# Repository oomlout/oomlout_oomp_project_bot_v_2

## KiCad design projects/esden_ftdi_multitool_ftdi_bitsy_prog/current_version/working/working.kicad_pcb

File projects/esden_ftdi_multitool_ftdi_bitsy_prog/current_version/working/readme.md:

# ftdi_multitool
 
## summary 
* id: esden_ftdi_multitool_ftdi_bitsy_prog
* user: esden
* name: ftdi_multitool
* board: ftdi_bitsy_prog
* repo: https://github.com/esden/ftdi-multitool
* src_file_repo_kicad_pcb: adapters/bitsy-prog/v1.0a/ftdi-bitsy-prog.kicad_pcb
* src_file_repo_kicad_pcb_link: https://github.com/esden/ftdi-multitool/tree/master/adapters/bitsy-prog/v1.0a/ftdi-bitsy-prog.kicad_pcb

* src_file_repo_sch: adapters/bitsy-prog/v1.0a/ftdi-bitsy-prog.sch
* src_file_repo_sch_link: https://github.com/esden/ftdi-multitool/tree/master/adapters/bitsy-prog/v1.0a/ftdi-bitsy-prog.sch
* full details link: https://github.com/oomlout/oomlout_oomp_project_bot_v_2/tree/main/projects/esden_ftdi_multitool_ftdi_bitsy_prog/current_version/working

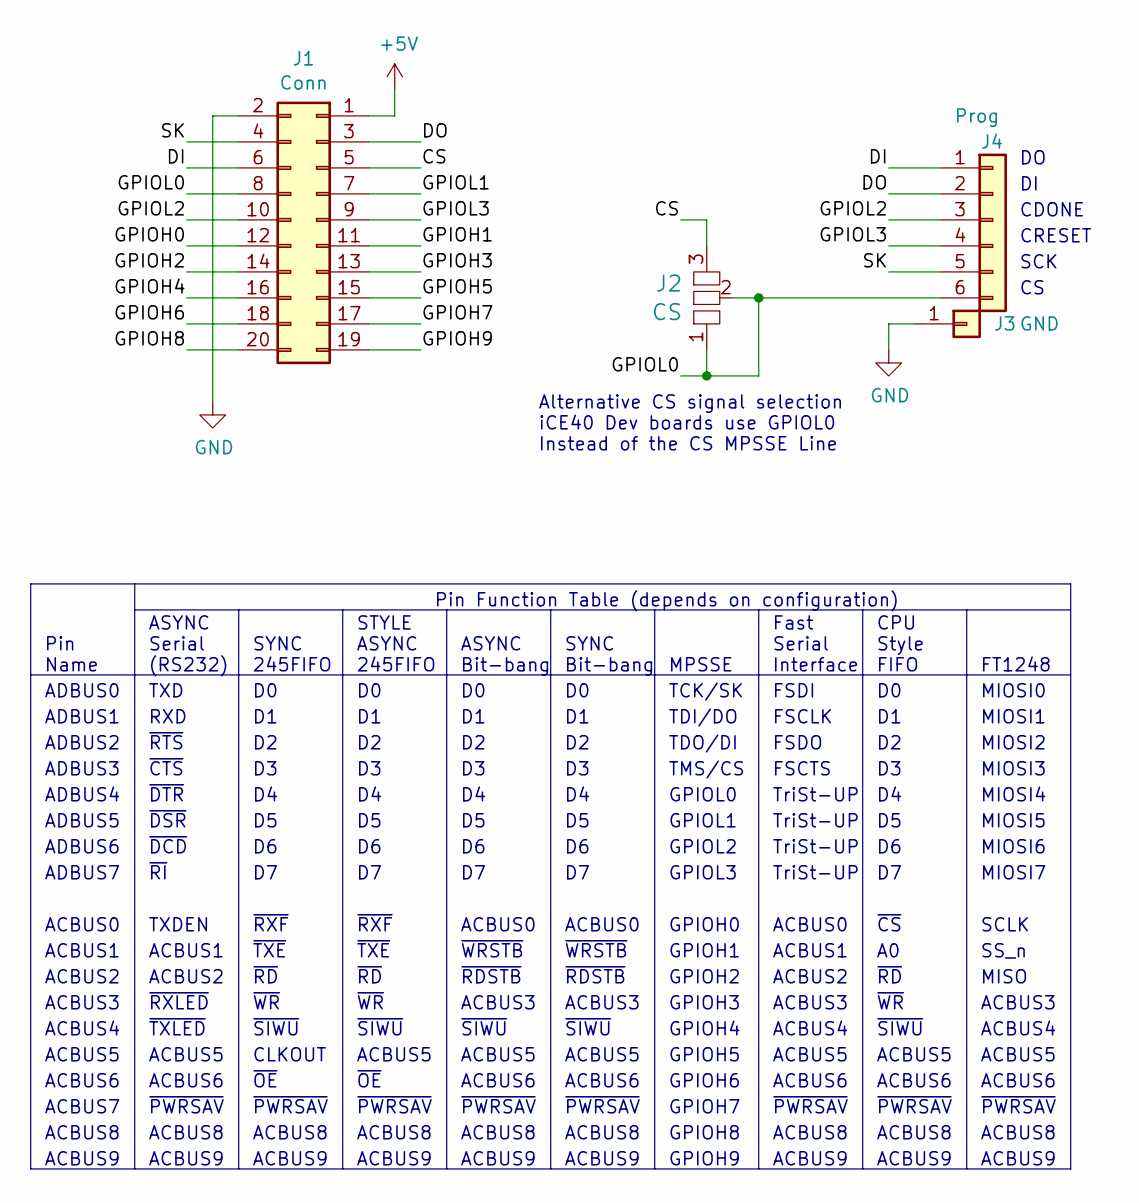
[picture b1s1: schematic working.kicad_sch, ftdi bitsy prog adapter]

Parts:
J1: Conn; FTSH-EDGE-20pin
J2: CS; J_0602
J3: GND; PinSocket_1x01_P2.54mm_Vertical
J4: Prog; PinSocket_1x06_P2.54mm_Vertical

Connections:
+5V: J1.1
/CS: J1.5, J2.3
/DI: J1.6, J4.1
/DO: J1.3, J4.2
/GPIOH0: J1.12
/GPIOH1: J1.11
/GPIOH2: J1.14
/GPIOH3: J1.13
/GPIOH4: J1.16
/GPIOH5: J1.15
/GPIOH6: J1.18
/GPIOH7: J1.17
/GPIOH8: J1.20
/GPIOH9: J1.19
/GPIOL0: J1.8, J2.1, J2.2, J4.6
/GPIOL1: J1.7
/GPIOL2: J1.10, J4.3
/GPIOL3: J1.9, J4.4
/SK: J1.4, J4.5
GND: J1.2, J3.1

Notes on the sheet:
ADBUS7
ACBUS6
~{RDSTB}
~{RTS}
ACBUS1
GPIOH8
GPIOH1
ACBUS9
~{RD}
SS_n
CPU Style FIFO
~{SIWU}
~{WRSTB}
ADBUS3
SCK
ACBUS5
~{OE}
~{CS}
GPIOL1
~{PWRSAV}
ACBUS8
MPSSE
TriSt-UP
GPIOH6
FSCLK
SYNC 245FIFO
RXD
ADBUS1
SYNC Bit-bang
~{WR}
Pin Name
~{CTS}
MIOSI6
GPIOL2
ACBUS3
~{TXE}
GPIOH5
TXDEN
TMS/CS
FSDO

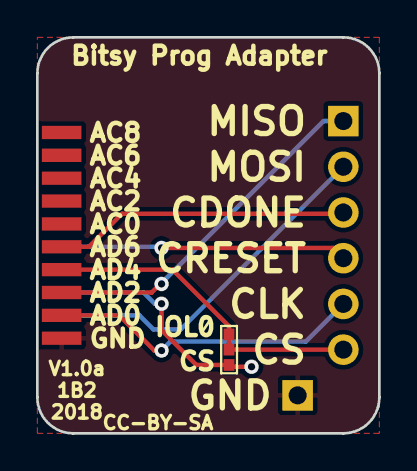
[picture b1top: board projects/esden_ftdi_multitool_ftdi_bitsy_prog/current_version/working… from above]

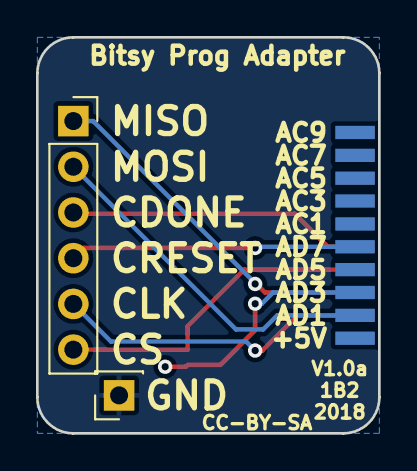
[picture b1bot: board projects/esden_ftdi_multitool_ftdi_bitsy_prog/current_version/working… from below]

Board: 2 copper layers, 19.0 x 22.0 mm, 4 parts (3 on the bottom side), 8 nets.

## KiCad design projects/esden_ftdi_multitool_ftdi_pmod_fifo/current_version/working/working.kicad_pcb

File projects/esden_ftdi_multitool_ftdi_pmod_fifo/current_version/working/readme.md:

# ftdi_multitool
 
## summary 
* id: esden_ftdi_multitool_ftdi_pmod_fifo
* user: esden
* name: ftdi_multitool
* board: ftdi_pmod_fifo
* repo: https://github.com/esden/ftdi-multitool
* src_file_repo_kicad_pcb: adapters/pmod-fifo/v1.0a/ftdi-pmod-fifo.kicad_pcb
* src_file_repo_kicad_pcb_link: https://github.com/esden/ftdi-multitool/tree/master/adapters/pmod-fifo/v1.0a/ftdi-pmod-fifo.kicad_pcb

* src_file_repo_sch: adapters/pmod-fifo/v1.0a/ftdi-pmod-fifo.sch
* src_file_repo_sch_link: https://github.com/esden/ftdi-multitool/tree/master/adapters/pmod-fifo/v1.0a/ftdi-pmod-fifo.sch
* full details link: https://github.com/oomlout/oomlout_oomp_project_bot_v_2/tree/main/projects/esden_ftdi_multitool_ftdi_pmod_fifo/current_version/working

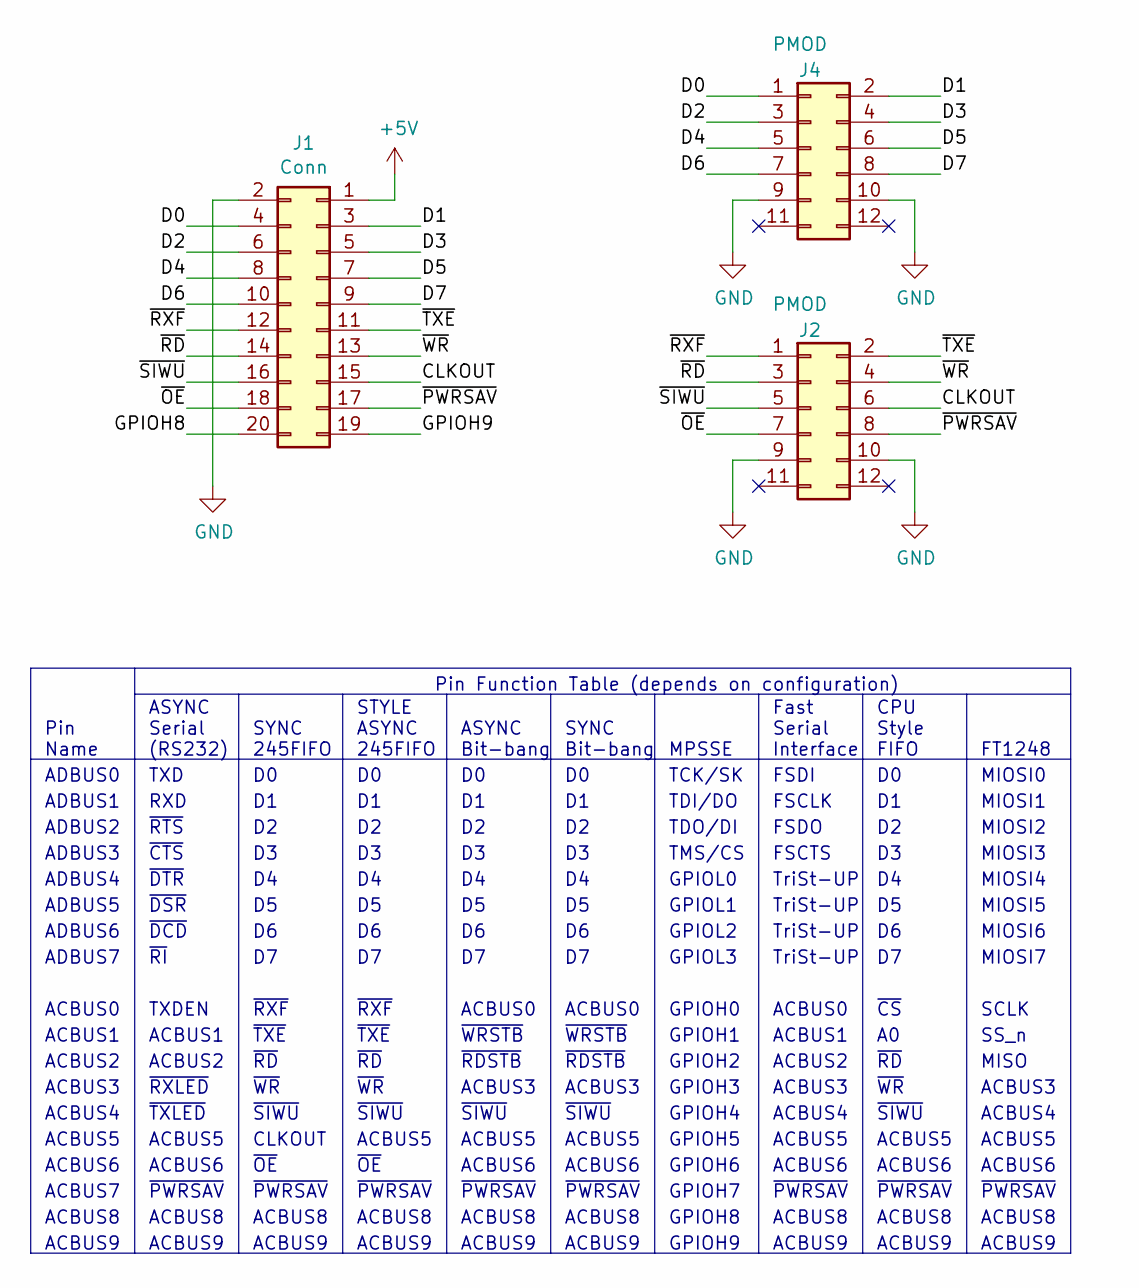
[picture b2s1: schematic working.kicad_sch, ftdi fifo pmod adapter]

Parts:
J1: Conn; FTSH-EDGE-20pin
J2, J4: PMOD; PinHeader_2x06_P2.54mm_Horizontal

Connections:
+5V: J1.1
/CLKOUT: J1.15, J2.6
/D0: J1.4, J4.1
/D1: J1.3, J4.2
/D2: J1.6, J4.3
/D3: J1.5, J4.4
/D4: J1.8, J4.5
/D5: J1.7, J4.6
/D6: J1.10, J4.7
/D7: J1.9, J4.8
/GPIOH8: J1.20
/GPIOH9: J1.19
/~OE: J1.18, J2.7
/~PWRSAV: J1.17, J2.8
/~RD: J1.14, J2.3
/~RXF: J1.12, J2.1
/~SIWU: J1.16, J2.5
/~TXE: J1.11, J2.2
/~WR: J1.13, J2.4
GND: J1.2, J2.9, J2.10, J4.9, J4.10

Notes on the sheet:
~{RTS}
~{WRSTB}
TriSt-UP
ACBUS1
FSDO
MIOSI5
ACBUS0
ACBUS8
~{PWRSAV}
GPIOL1
RXD
TXDEN
~{SIWU}
~{RXLED}
ACBUS5
ACBUS4
ACBUS9
~{WR}
GPIOH5
ACBUS2
ACBUS6
~{OE}
ACBUS3
~{TXE}
Pin Function Table (depends on configuration)
SCLK
MIOSI3
~{CS}
ADBUS5
TDI/DO
TMS/CS
STYLE ASYNC 245FIFO
Pin Name
GPIOH3
ADBUS1
~{RDSTB}
FSCTS
GPIOL0
~{DCD}
~{DTR}

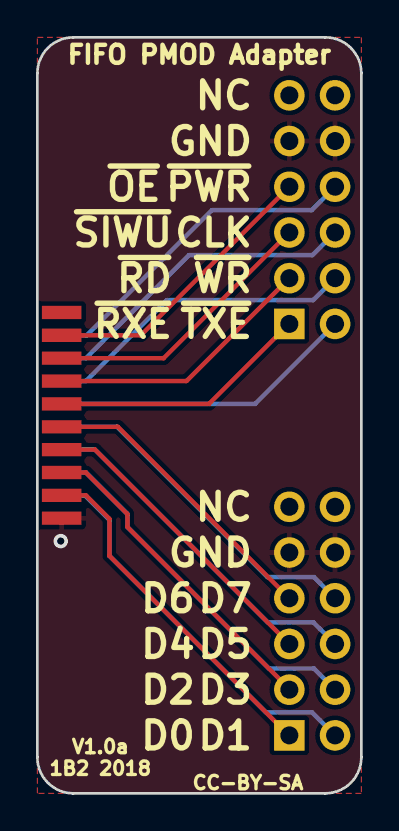
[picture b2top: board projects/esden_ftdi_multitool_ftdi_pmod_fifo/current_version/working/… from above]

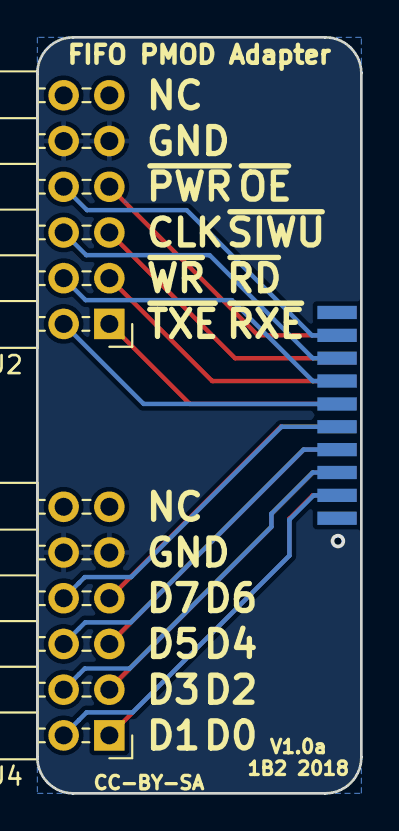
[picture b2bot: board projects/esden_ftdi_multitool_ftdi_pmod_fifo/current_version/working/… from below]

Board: 2 copper layers, 18.0 x 42.0 mm, 3 parts (3 on the bottom side), 17 nets.

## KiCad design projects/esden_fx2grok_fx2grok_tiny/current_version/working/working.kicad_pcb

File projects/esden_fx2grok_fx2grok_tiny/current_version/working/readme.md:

# fx2grok
 
## summary 
* id: esden_fx2grok_fx2grok_tiny
* user: esden
* name: fx2grok
* board: fx2grok_tiny
* repo: https://github.com/esden/fx2grok
* src_file_repo_kicad_pcb: hardware/fx2grok-tiny/0.2/fx2grok-tiny.kicad_pcb
* src_file_repo_kicad_pcb_link: https://github.com/esden/fx2grok/tree/master/hardware/fx2grok-tiny/0.2/fx2grok-tiny.kicad_pcb

* src_file_repo_sch: hardware/fx2grok-tiny/0.2/fx2grok-tiny.sch
* src_file_repo_sch_link: https://github.com/esden/fx2grok/tree/master/hardware/fx2grok-tiny/0.2/fx2grok-tiny.sch
* full details link: https://github.com/oomlout/oomlout_oomp_project_bot_v_2/tree/main/projects/esden_fx2grok_fx2grok_tiny/current_version/working

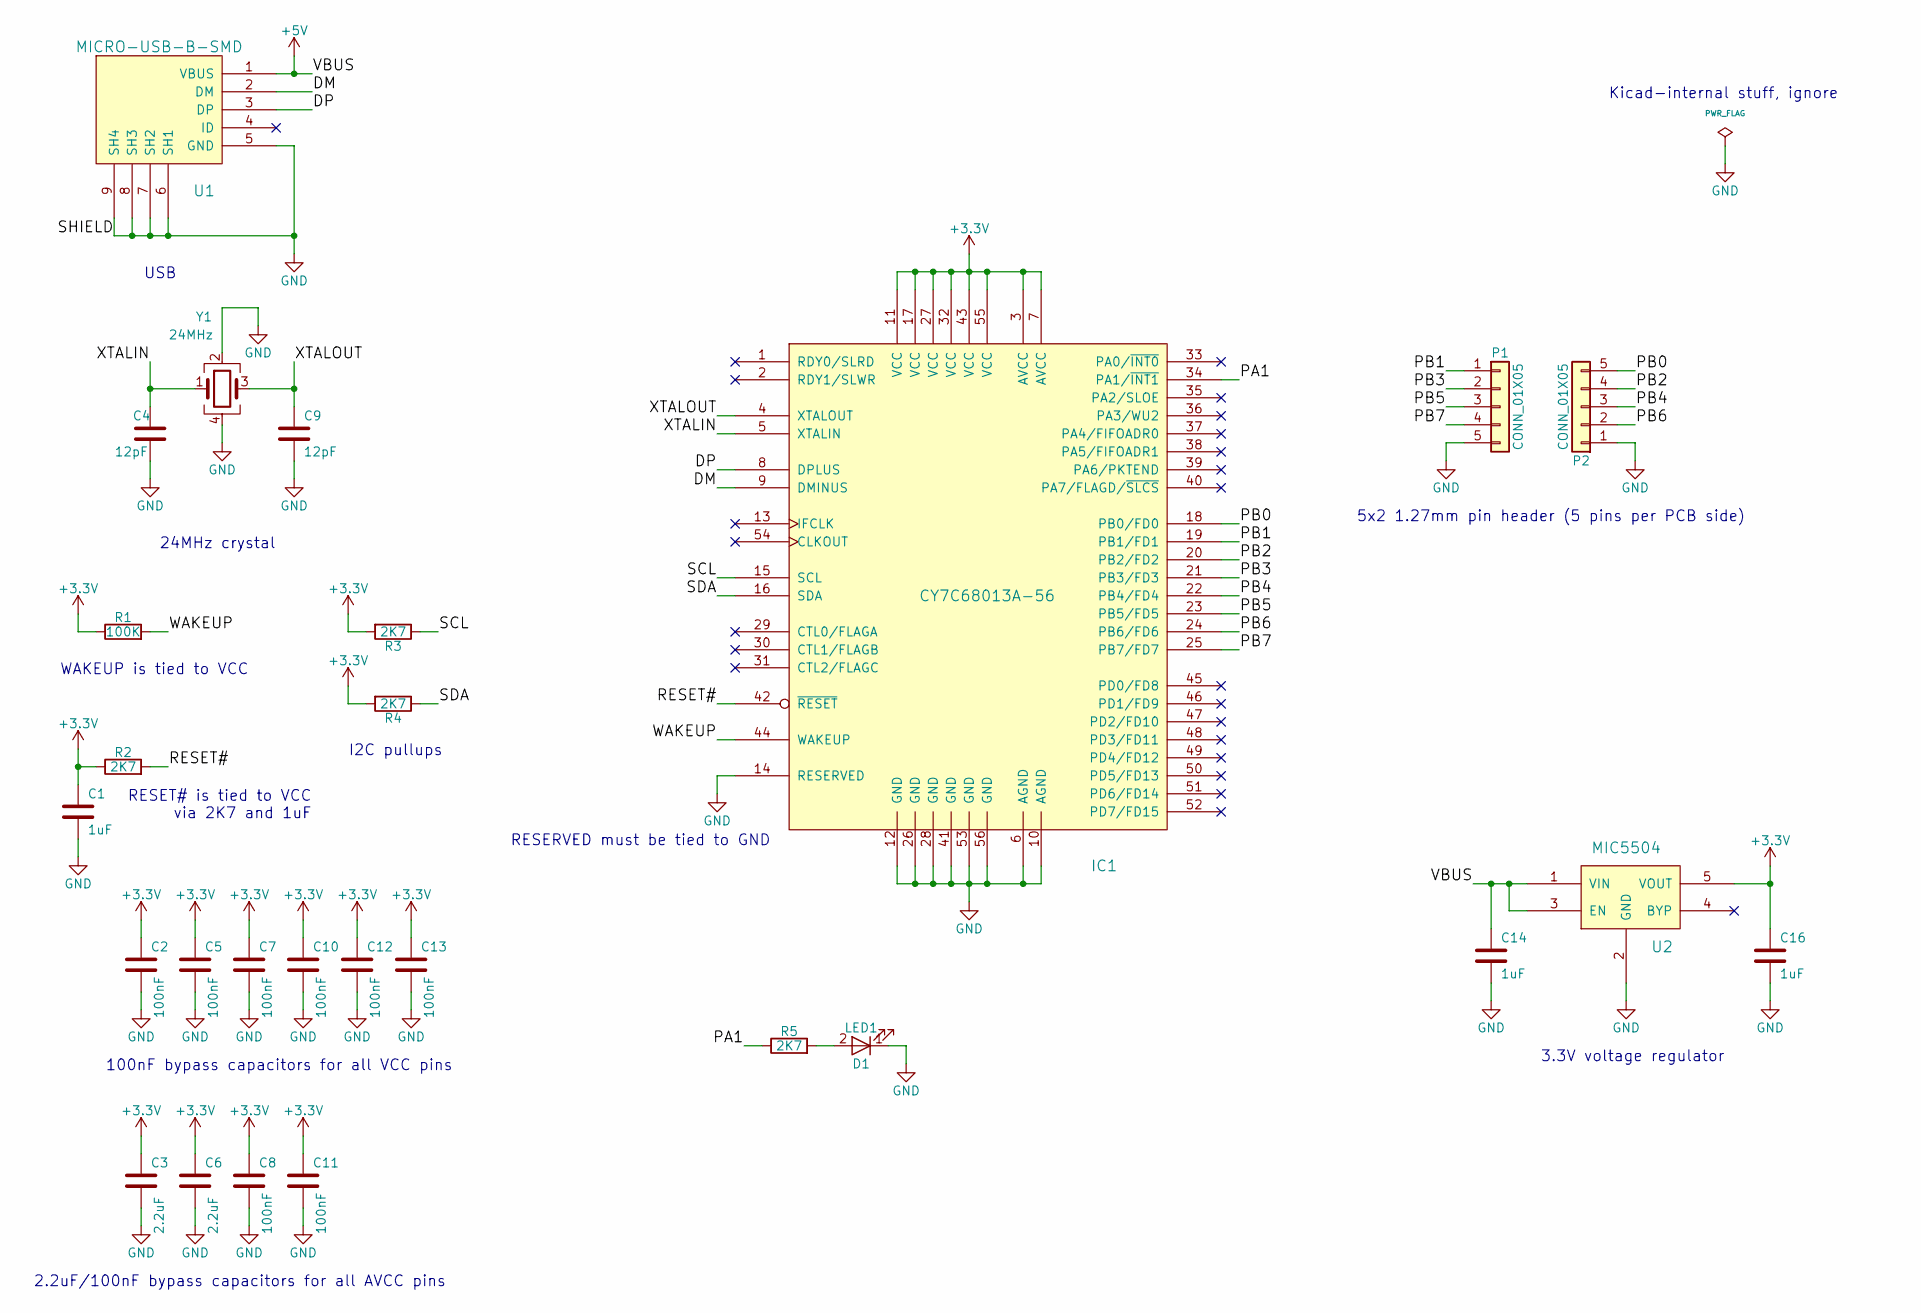
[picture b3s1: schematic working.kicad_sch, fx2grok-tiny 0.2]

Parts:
C1, C14, C16: 1uF; SM0402
C2, C5, C7, C8, C10, C11, C12, C13: 100nF; SM0402
C3, C6: 2.2uF; SM0402
C4, C9: 12pF; SM0402
D1: LED1; SM0402
IC1: CY7C68013A-56; QFN56
P1, P2: CONN_01X05; CONN-5x1-SMD-127MM
R1: 100K; SM0402
R2, R3, R4, R5: 2K7; SM0402
U1: MICRO-USB-B-SMD
U2: MIC5504; SOT23-5
Y1: 24MHz; ABM11

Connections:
+3V3: C1.1, C2.1, C3.1, C5.1, C6.1, C7.1, C8.1, C10.1, C11.1, C12.1, C13.1, C16.1, IC1.3 (AVCC), IC1.7 (AVCC), IC1.11 (VCC), IC1.17 (VCC), IC1.27 (VCC), IC1.32 (VCC), IC1.43 (VCC), IC1.55 (VCC), R1.1, R2.1, R3.2, R4.2, U2.5 (VOUT)
+5V: C14.1, U1.1 (VBUS), U2.1 (VIN), U2.3 (EN)
/DM: IC1.9 (DMINUS), U1.2 (DM)
/DP: IC1.8 (DPLUS), U1.3 (DP)
/PA1: IC1.34 (PA1/~INT1), R5.1
/PB0: IC1.18 (PB0/FD0), P2.5
/PB1: IC1.19 (PB1/FD1), P1.1
/PB2: IC1.20 (PB2/FD2), P2.4
/PB3: IC1.21 (PB3/FD3), P1.2
/PB4: IC1.22 (PB4/FD4), P2.3
/PB5: IC1.23 (PB5/FD5), P1.3
/PB6: IC1.24 (PB6/FD6), P2.2
/PB7: IC1.25 (PB7/FD7), P1.4
/RESET#: IC1.42 (~RESET), R2.2
/SCL: IC1.15 (SCL), R3.1
/SDA: IC1.16 (SDA), R4.1
/WAKEUP: IC1.44 (WAKEUP), R1.2
/XTALIN: C4.1, IC1.5 (XTALIN), Y1.1
/XTALOUT: C9.1, IC1.4 (XTALOUT), Y1.3
GND: C1.2, C2.2, C3.2, C4.2, C5.2, C6.2, C7.2, C8.2, C9.2, C10.2, C11.2, C12.2, C13.2, C14.2, C16.2, D1.1 (K), IC1.6 (AGND), IC1.10 (AGND), IC1.12 (GND), IC1.14 (RESERVED), IC1.26 (GND), IC1.28 (GND), IC1.41 (GND), IC1.53 (GND), IC1.56 (GND), P1.5, P2.1, U1.5 (GND), U1.6 (SH1), U1.7 (SH2), U1.8 (SH3), U1.9 (SH4), U2.2 (GND), Y1.2, Y1.4
unnamed: D1.2 (A), R5.2

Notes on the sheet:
RESERVED must be tied to GND
RESET# is tied to VCC via 2K7 and 1uF
WAKEUP is tied to VCC
I2C pullups
2.2uF/100nF bypass capacitors for all AVCC pins
Kicad-internal stuff, ignore
5x2 1.27mm pin header (5 pins per PCB side)
100nF bypass capacitors for all VCC pins
24MHz crystal
USB
3.3V voltage regulator

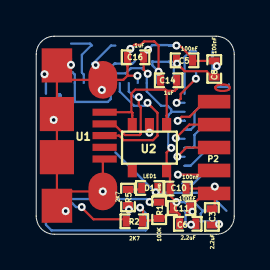
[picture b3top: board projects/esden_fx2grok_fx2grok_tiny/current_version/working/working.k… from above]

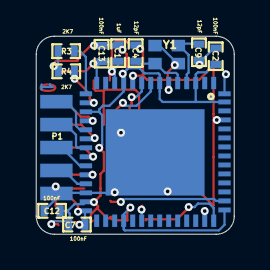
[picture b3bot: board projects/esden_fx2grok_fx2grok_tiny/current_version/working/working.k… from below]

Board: 2 copper layers, 11.0 x 11.0 mm, 27 parts (12 on the bottom side), 21 nets.

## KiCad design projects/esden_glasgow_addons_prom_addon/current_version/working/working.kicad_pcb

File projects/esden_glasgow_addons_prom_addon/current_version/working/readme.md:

# glasgow_addons
 
## summary 
* id: esden_glasgow_addons_prom_addon
* user: esden
* name: glasgow_addons
* board: prom_addon
* repo: https://github.com/esden/glasgow-addons
* src_file_repo_kicad_pcb: hardware/prom-addon/prom-addon.kicad_pcb
* src_file_repo_kicad_pcb_link: https://github.com/esden/glasgow-addons/tree/master/hardware/prom-addon/prom-addon.kicad_pcb

* src_file_repo_sch: hardware/prom-addon/prom-addon.sch
* src_file_repo_sch_link: https://github.com/esden/glasgow-addons/tree/master/hardware/prom-addon/prom-addon.sch
* full details link: https://github.com/oomlout/oomlout_oomp_project_bot_v_2/tree/main/projects/esden_glasgow_addons_prom_addon/current_version/working

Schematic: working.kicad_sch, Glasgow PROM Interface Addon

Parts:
C1, C2: 100n; C_0402
J1, J2: Conn_02x10_Odd_Even; PinSocket_2x10_P2.54mm_Vertical
JP1, JP2: Pin Mode; PinHeader_1x03_P2.54mm_Vertical
RN1, RN2, RN3: 33R; R_Array_Convex_4x0402
U1, U2: 74HC595; DHVQFN-16_2.5x3.5mm_Pitch0.5mm
U3: 27C512; DIP-28_W15.24mm

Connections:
/A0: J1.3, U3.10 (A0)
/A1: J1.5, U3.9 (A1)
/A2: J1.7, U3.8 (A2)
/A3: J1.9, U3.7 (A3)
/A4: RN1.1 (R1.1), U3.6 (A4)
/A5: RN1.2 (R2.1), U3.5 (A5)
/A6: RN1.3 (R3.1), U3.4 (A6)
/A7: RN1.4 (R4.1), U3.3 (A7)
/A8: RN2.1 (R1.1), U3.25 (A8)
/A9: RN2.2 (R2.1), U3.24 (A9)
/A10: RN2.3 (R3.1), U3.21 (A10)
/A11: RN2.4 (R4.1), U3.23 (A11)
/A12: RN3.1 (R1.1), U3.2 (A12)
/A13: RN3.2 (R2.1), U3.26 (A13)
/A14: JP1.1 (A), RN3.3 (R3.1)
/A15: JP2.1 (A), RN3.4 (R4.1)
/A_CLK: J1.11, U1.11, U2.11
/A_LATCH: J1.13, U1.12, U2.12
/A_SI: J1.15, U1.14
/A_SI´: U1.9, U2.14
/DQ0: J2.3, U3.11 (D0)
/DQ1: J2.5, U3.12 (D1)
/DQ2: J2.7, U3.13 (D2)
/DQ3: J2.9, U3.15 (D3)
/DQ4: J2.11, U3.16 (D4)
/DQ5: J2.13, U3.17 (D5)
/DQ6: J2.15, U3.18 (D6)
/DQ7: J2.17, U3.19 (D7)
/P1: JP2.2 (C), U3.1 (A15)
/P27: JP1.2 (C), U3.27 (A14)
/~OE: J1.17, U3.20 (~CE), U3.22 (~OE)
GND: C1.2, C2.2, J1.4, J1.6, J1.8, J1.10, J1.12, J1.14, J1.16, J1.18, J2.4, J2.6, J2.8, J2.10, J2.12, J2.14, J2.16, J2.18, JP2.3 (B), U1.8, U1.13, U1.17, U2.8, U2.13, U2.17, U3.14 (GND)
unnamed: RN1.5 (R4.2), U1.3
unnamed: RN1.6 (R3.2), U1.2
unnamed: RN1.7 (R2.2), U1.1
unnamed: RN1.8 (R1.2), U1.15
unnamed: RN2.5 (R4.2), U1.7
unnamed: RN2.6 (R3.2), U1.6
unnamed: RN2.7 (R2.2), U1.5
unnamed: RN2.8 (R1.2), U1.4
unnamed: RN3.5 (R4.2), U2.3
unnamed: RN3.6 (R3.2), U2.2
unnamed: RN3.7 (R2.2), U2.1
unnamed: RN3.8 (R1.2), U2.15
VCC: C1.1, C2.1, J1.1, J1.2, J2.1, J2.2, JP1.3 (B), U1.10, U1.16, U2.10, U2.16, U3.28 (VCC)

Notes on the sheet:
Can be Vpp or A15
Can be ~{PGM} or A14

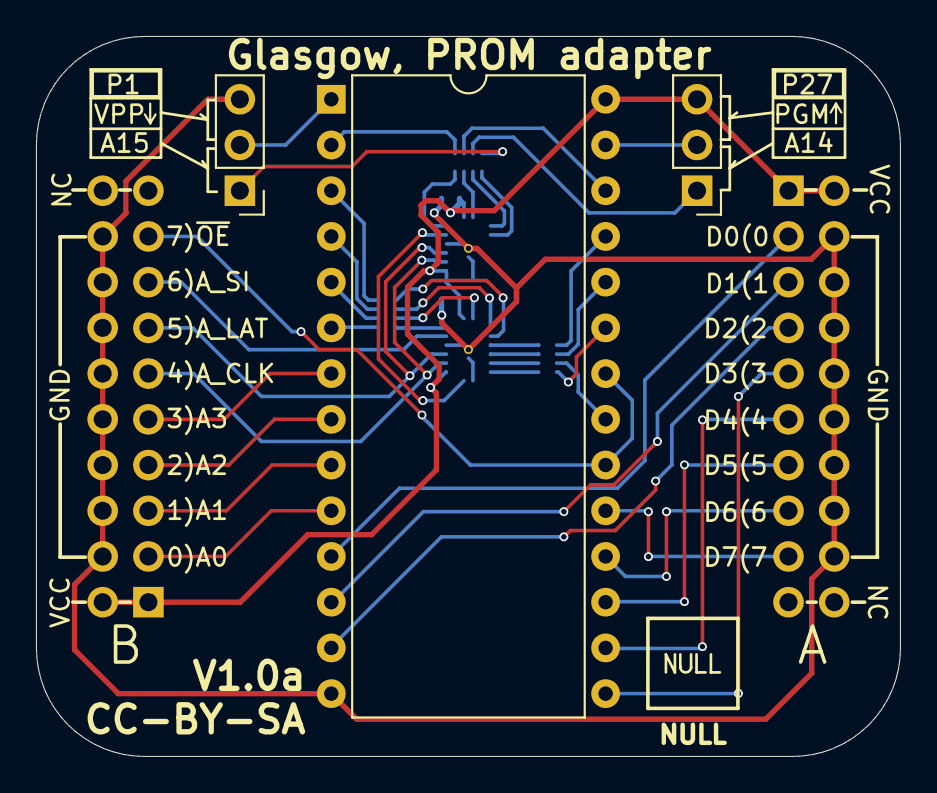
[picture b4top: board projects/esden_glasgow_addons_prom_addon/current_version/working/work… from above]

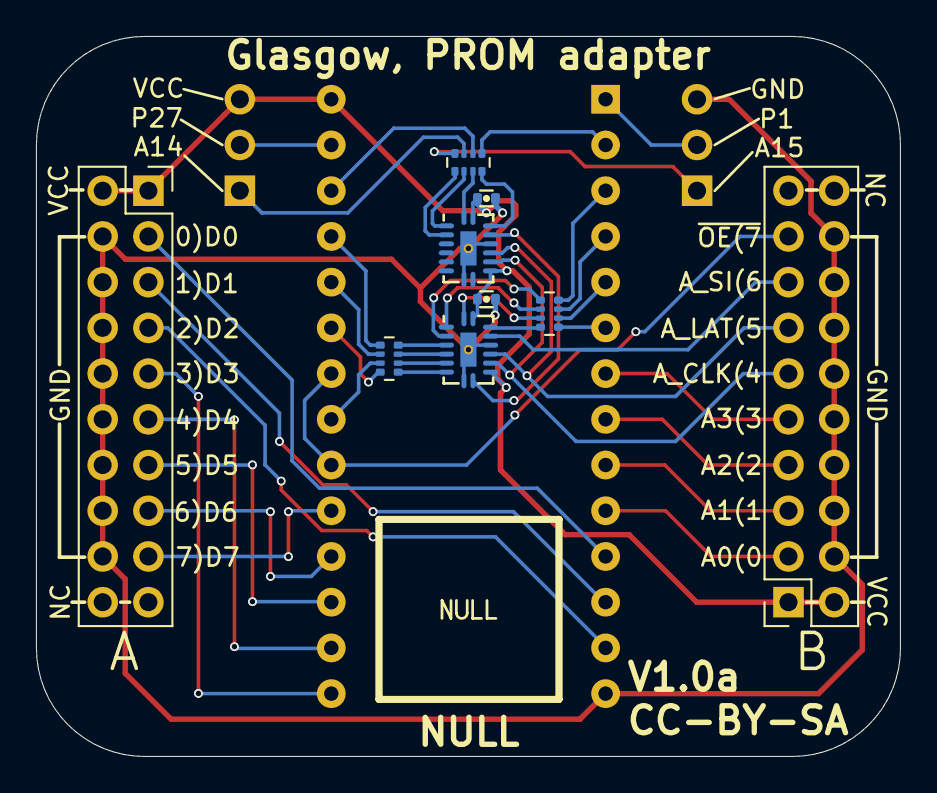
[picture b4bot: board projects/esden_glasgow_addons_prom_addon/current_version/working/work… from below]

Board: 2 copper layers, 48.0 x 40.0 mm, 12 parts (9 on the bottom side), 45 nets.

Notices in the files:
projects/esden_ftdi_multitool_ftdi_100mil/current_version/working/working.kicad_sch:
License: CC-BY-SA 4.0
projects/esden_ftdi_multitool_ftdi_bitsy_prog/current_version/working/working.kicad_pcb:
CC-BY-SA
projects/esden_fx2grok_fx2grok_tiny/current_version/working/working.kicad_pcb:
Open Hardware, CC-BY-SA 4.0
projects/esden_glasgow_addons_prom_addon/current_version/working/working.kicad_pcb:
(C) 2020-2021 1BitSquared
(C) 2020-2021 Piotr Esden-Tempski
